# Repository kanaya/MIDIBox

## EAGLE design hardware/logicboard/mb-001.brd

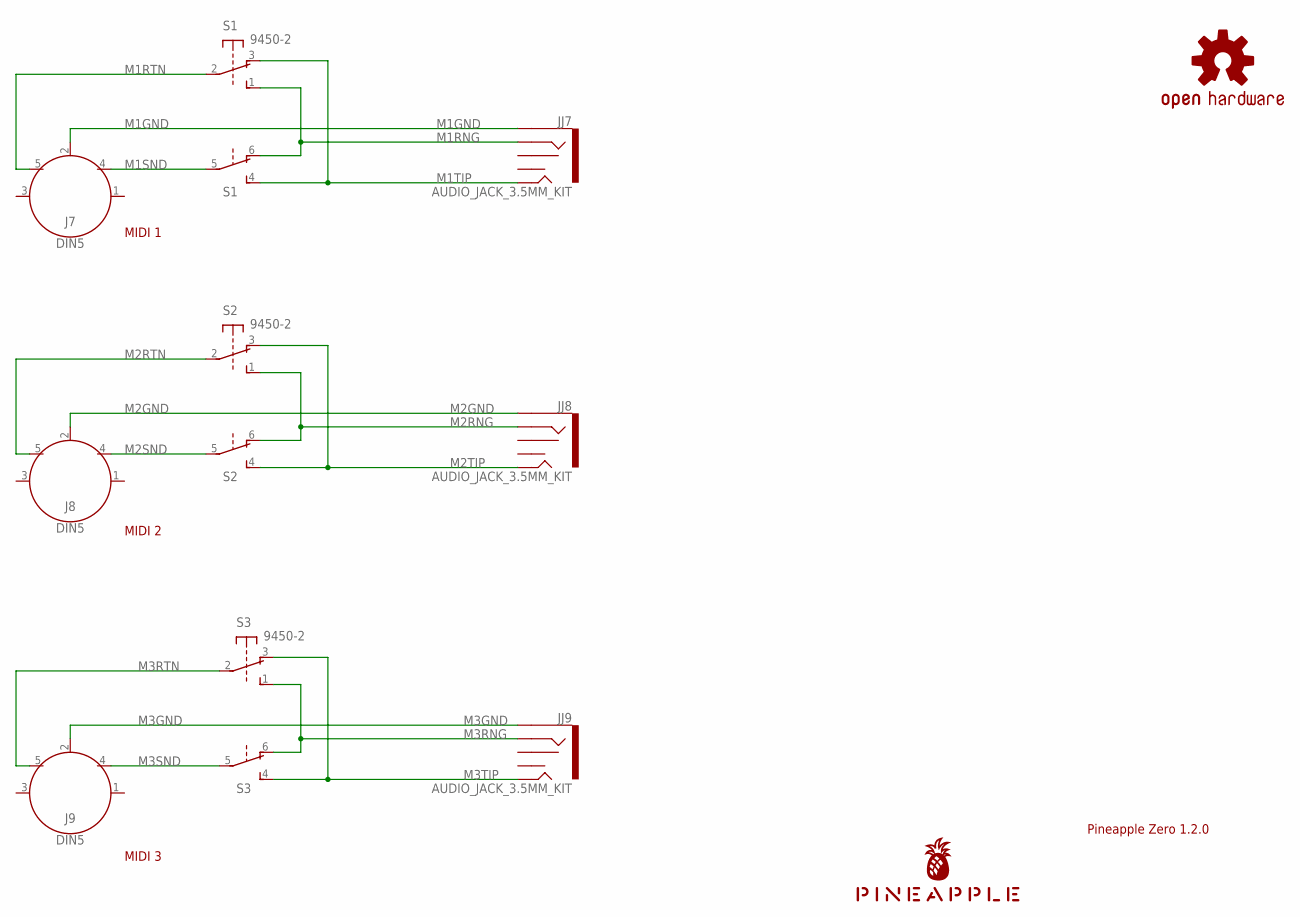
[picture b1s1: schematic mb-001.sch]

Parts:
J7, J8, J9: DIN5; DIN5-RA-PTH
JJ7, JJ8, JJ9: AUDIO_JACK_3.5MM_KIT; AUDIO-JACK-KIT
LOGO1: OSHW-LOGOS-COPPER; OSHW-LOGO-S_COPPER
S1, S2, S3: 9450-2
U$1: PINEAPPLE450

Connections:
M1GND: J7.2, JJ7.SLEEVE
M1RING: JJ7.TIP, S1.3 (O), S1.4 (S)
M1RTN: J7.5, S1.2
M1SND: J7.4, S1.5
M1TIP: JJ7.RING, S1.1 (S), S1.6 (O)
M2GND: J8.2, JJ8.SLEEVE
M2RING: JJ8.TIP, S2.3 (O), S2.4 (S)
M2RTN: J8.5, S2.2
M2SND: J8.4, S2.5
M2TIP: JJ8.RING, S2.1 (S), S2.6 (O)
M3GND: J9.2, JJ9.SLEEVE
M3RING: JJ9.TIP, S3.3 (O), S3.4 (S)
M3RTN: J9.5, S3.2
M3SND: J9.4, S3.5
M3TIP: JJ9.RING, S3.1 (S), S3.6 (O)

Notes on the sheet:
Pineapple Zero 1.2.0
MIDI 1
MIDI 3
MIDI 2

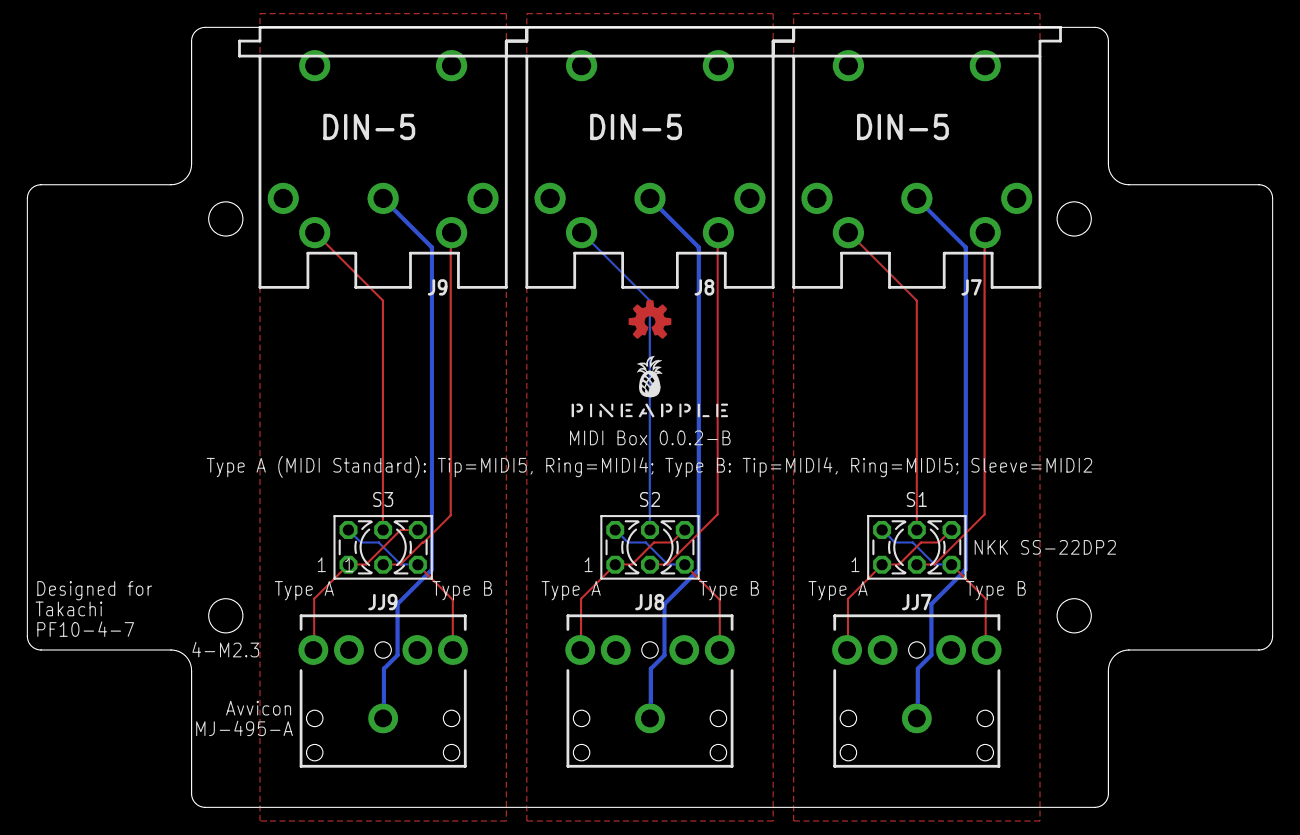
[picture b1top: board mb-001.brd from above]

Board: 2 copper layers, 91.0 x 57.0 mm, 11 parts (0 on the bottom side), 15 nets.

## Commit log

2022-08-11 Imported from Pineapple Zero 2.0.1-B.
2022-08-11 Initial design.
2022-08-11 Silk.
2022-08-11 Type A/B Sw.
2022-08-11 GND patterns.
2022-08-11 Align of TRS jacks.
2022-08-15 Symbol name.
2022-10-14 Fixed silk and signal names. No pattern changed.

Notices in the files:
parts and their libraries:
SparkFun-Aesthetics: Licensing: Creative Commons ShareAlike 4.0 International - https://creativecommons.org/licenses/by-sa/4.0
